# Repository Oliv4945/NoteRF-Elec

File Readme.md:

# NodeRF

RF sensors and actuators based on ATMega328 and RFM69hw from hopeRF.  
Arduino bootloader is used in order to use all available libraries

## NoteGateway
Gateway with serial output. It just collects data from RF sensors and send it through serial link.  
Configuration is explained in configuration.h file

Serial messages are really simple for now and formated like `sensorNumber|dataType|Data1|Data2|DataX|batteryLevel|RSSI`  
For example, the sensor N°5, type temperature (16.50°C) and humidity (55.3%) with a battery level of 3.98V is `5|1|1650|5530|398|-53`

## NoteSensor
Sensors' code.  
You just have to set config.h to suit your needs. Also uncommenting a `#define DATA_SENSORNAME` will activate it.

## Schematics
Hardware source files made with Eagle 7.3.0 + [Spakfun library](https://github.com/sparkfun/SparkFun-Eagle-Libraries)

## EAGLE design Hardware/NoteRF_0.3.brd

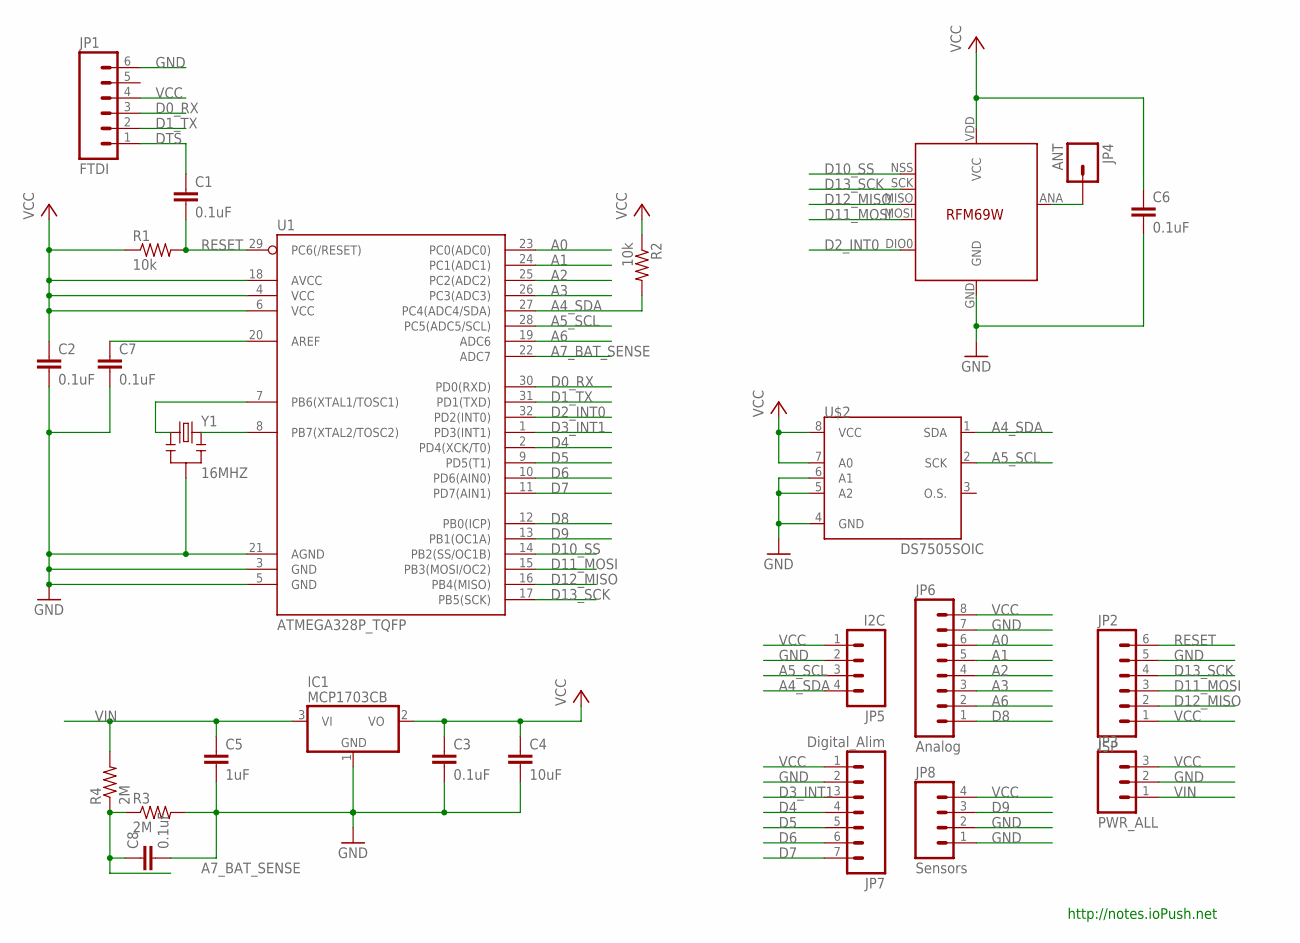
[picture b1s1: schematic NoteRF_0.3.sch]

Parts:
C1, C2, C3, C6, C7, C8: 0.1uF; 0805
C4: 10uF; 0805
C5: 1uF; 0805
IC1: MCP1703CB; SOT23
JP1: FTDI; 1X06_LOCK
JP2: ISP; 1X06_LOCK
JP3: PWR_ALL; 1X03_LOCK
JP4: ANT; 1X01NS-KIT
JP5: I2C; 1X04_LOCK
JP6: Analog; 1X08_LOCK
JP7: Digital_Alim; 1X07_LOCK
JP8: Sensors; 1X04_LOCK
R1, R2: 10k; 0805
R3, R4: 2M; 0805
U1: ATMEGA328P_TQFP; TQFP32-08
U$1: RFM69; RFM69W-MINPADS
U$2: DS7505SOIC; SO08
Y1: 16MHZ; RESONATOR-SMD

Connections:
A0: JP6.6, U1.23 (PC0(ADC0))
A1: JP6.5, U1.24 (PC1(ADC1))
A2: JP6.4, U1.25 (PC2(ADC2))
A3: JP6.3, U1.26 (PC3(ADC3))
A4_SDA: JP5.4, R2.2, U1.27 (PC4(ADC4/SDA)), U$2.1 (SDA)
A5_SCL: JP5.3, U1.28 (PC5(ADC5/SCL)), U$2.2 (SCK)
A6: JP6.2, U1.19 (ADC6)
A7_BAT_SENSE: C8.1, R3.1, R4.1, U1.22 (ADC7)
D0_RX: JP1.3, U1.30 (PD0(RXD))
D1_TX: JP1.2, U1.31 (PD1(TXD))
D2_INT0: U1.32 (PD2(INT0)), U$1.DIO0
D3_INT1: JP7.3, U1.1 (PD3(INT1))
D4: JP7.4, U1.2 (PD4(XCK/T0))
D5: JP7.5, U1.9 (PD5(T1))
D6: JP7.6, U1.10 (PD6(AIN0))
D7: JP7.7, U1.11 (PD7(AIN1))
D8: JP6.1, U1.12 (PB0(ICP))
D9: JP8.3, U1.13 (PB1(OC1A))
D10_SS: U1.14 (PB2(SS/OC1B)), U$1.NSS (SEL)
D11_MOSI: JP2.3, U1.15 (PB3(MOSI/OC2)), U$1.MOSI
D12_MISO: JP2.2, U1.16 (PB4(MISO)), U$1.MISO
D13_SCK: JP2.4, U1.17 (PB5(SCK)), U$1.SCK
DTS: C1.1, JP1.1
GND: C2.2, C3.2, C4.2, C5.2, C6.2, C7.2, C8.2, IC1.1 (GND), JP1.6, JP2.5, JP3.2, JP5.2, JP6.7, JP7.2, JP8.1, JP8.2, R3.2, U1.3 (GND), U1.5 (GND), U1.21 (AGND), U$1.GND, U$2.4 (GND), U$2.5 (A2), U$2.6 (A1), Y1.2
unnamed: JP4.1, U$1.ANA (ANT)
unnamed: C7.1, U1.20 (AREF)
unnamed: U1.8 (PB7(XTAL2/TOSC2)), Y1.3
unnamed: U1.7 (PB6(XTAL1/TOSC1)), Y1.1
RESET: C1.2, JP2.6, R1.2, U1.29 (PC6(/RESET))
VCC: C2.1, C3.1, C4.1, C6.1, IC1.2 (VO), JP1.4, JP2.1, JP3.3, JP5.1, JP6.8, JP7.1, JP8.4, R1.1, R2.1, U1.4 (VCC), U1.6 (VCC), U1.18 (AVCC), U$1.VDD (VCC), U$2.7 (A0), U$2.8 (VCC)
VIN: C5.1, IC1.3 (VI), JP3.1, R4.2

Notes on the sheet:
http://notes.ioPush.net

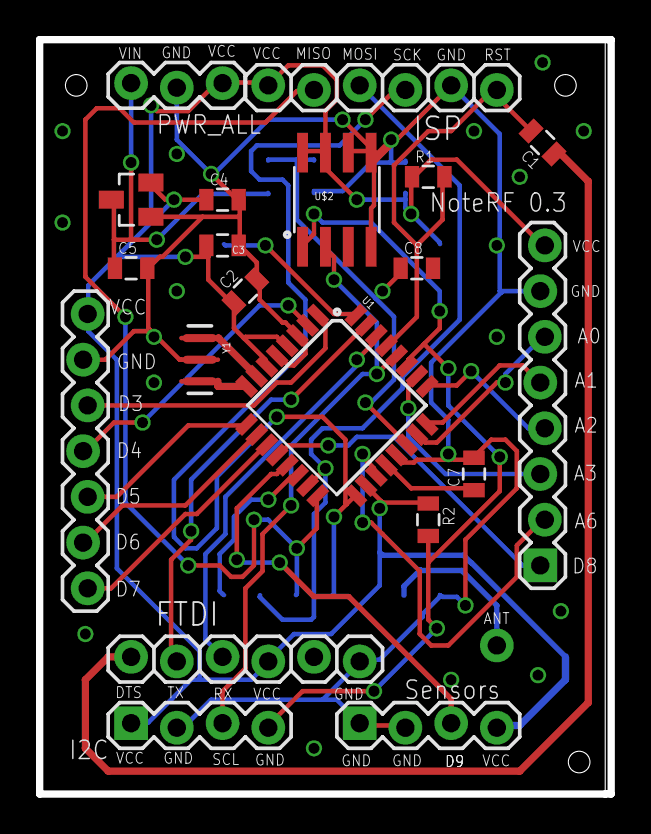
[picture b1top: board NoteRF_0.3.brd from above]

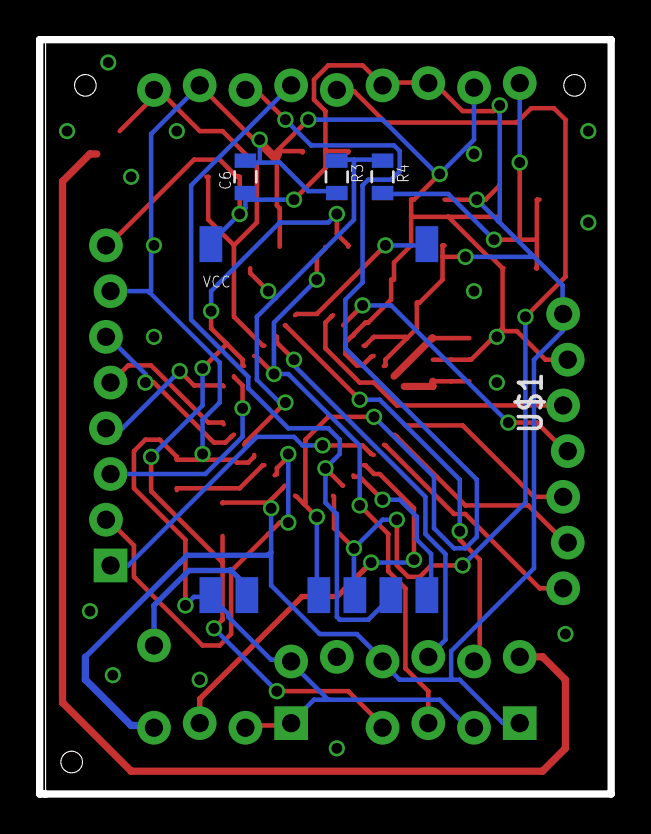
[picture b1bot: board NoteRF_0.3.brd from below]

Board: 2 copper layers, 31.8 x 41.9 mm, 25 parts (4 on the bottom side), 31 nets.

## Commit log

2015-03-05 Project initialisation
2015-03-05 Typo in .gitignore
2015-03-05 Add Readme.md file
2015-03-05 Add Readme.md for sub folders
2015-03-07 Gateway and node Add "configuration.h" file for improving configuration Add #define DATA_SENSOR for each sensor, improving configuration
    Gateway
    Send data type through serial link to allow the receiver to understand what is send
2015-03-07 Update readme for new configuration
2015-03-07 Improve NoteSensor readability
2015-03-08 Avoid error on first DHT22 reading in loop()
2015-03-09 Bug correction : wrong constant
2015-03-09 Both: Add téléinformation client
    Gateway:
    Add informations about network on startup
    Node:
    Change default debug configuration (not activated)
2015-03-13 Added moisture sensor Disable all sensor by default
2015-03-14 Code improvements and bug correction
    Both
    Gateway
    Sending 'RADIO.DATALEN', better to understand than 'i' variable
    Node
    Display program name and node ID at startup
    Remove unused variable and move sensor specific inside '#ifdef'
2015-09-26 Add BMPXXX barometric pressure sensor
2016-01-06 Add gateway info
2016-01-08 Add NoteSensor comments
2016-01-08 Remove not needed Readme.md
2016-02-01 Add hardware source files NoteRF V0.3
2016-02-01 Update Readme.md with hardware sources
2020-02-14 Switch to PIO & add ST tof sensor
2020-02-14 Switch gateway to PIO

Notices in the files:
parts and their libraries:
SparkFun-Passives: Licensing: Creative Commons ShareAlike 4.0 International - https://creativecommons.org/licenses/by-sa/4.0
